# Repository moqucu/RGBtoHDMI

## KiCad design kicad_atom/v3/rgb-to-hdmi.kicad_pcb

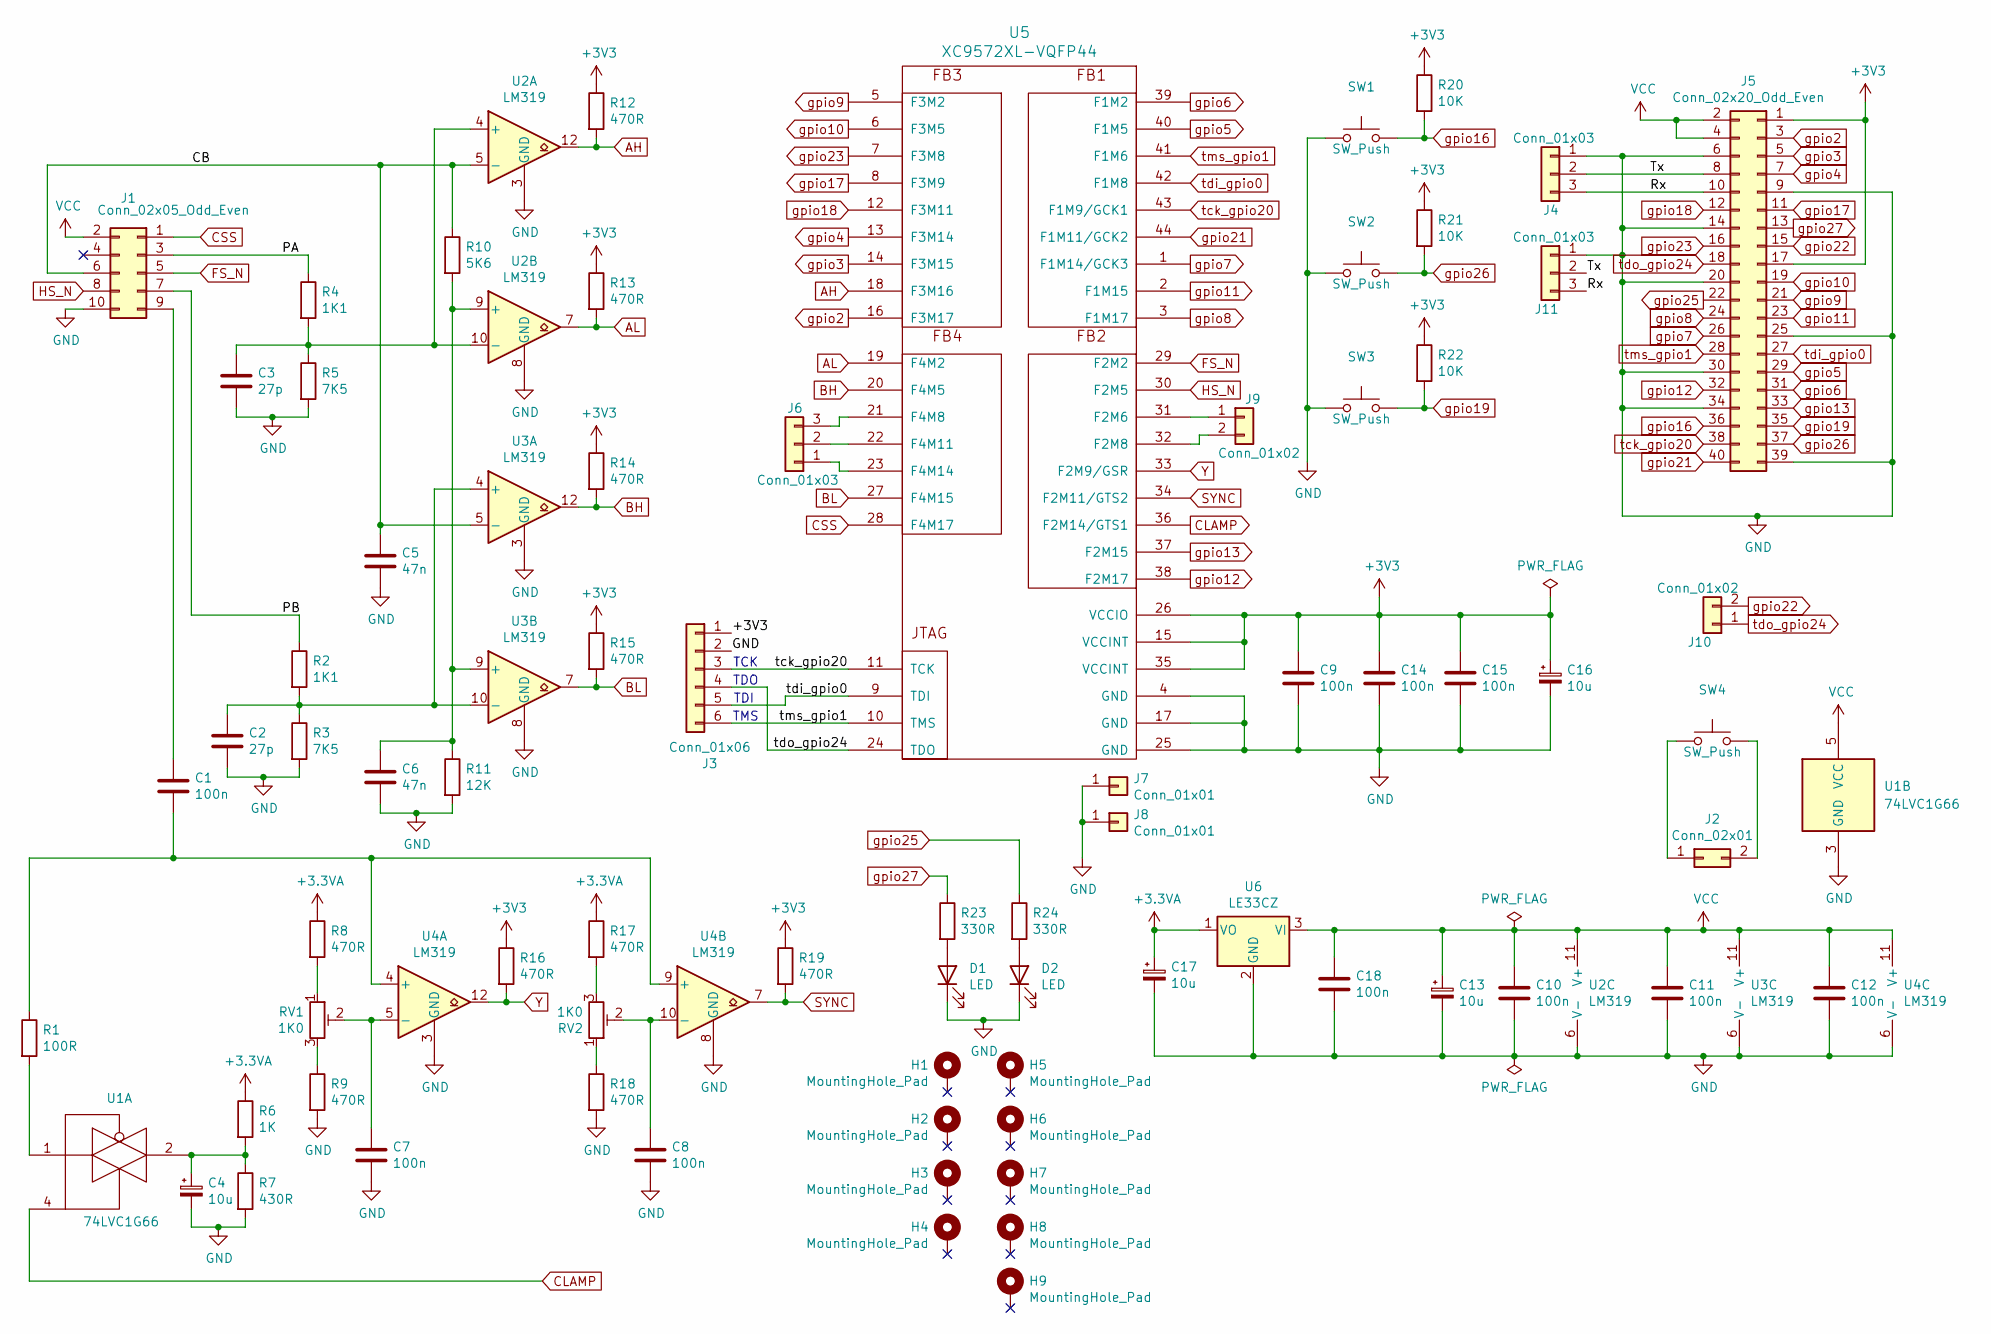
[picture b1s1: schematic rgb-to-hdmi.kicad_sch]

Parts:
C1, C7, C8, C18: 100n; C_Rect_L7.0mm_W2.5mm_P5.00mm
C2, C3: 27p; C_Rect_L7.0mm_W2.5mm_P5.00mm
C4, C13, C16, C17: 10u; CP_Radial_D5.0mm_P2.50mm
C5, C6: 47n; C_Rect_L7.0mm_W2.5mm_P5.00mm
C9, C14, C15: 100n; C_0805_2012Metric_Pad1.18x1.45mm_HandSolder
C10, C11, C12: 100n; C_Axial_L5.1mm_D3.1mm_P10.00mm_Horizontal
D1, D2: LED; LED_D3.0mm
H1, H2, H3, H4, H5, H6, H7, H8, H9: MountingHole_Pad; MountingHole_2.7mm_M2.5_Pad
J1: Conn_02x05_Odd_Even; IDC-Header_2x05_P2.54mm_Vertical
J2: Conn_02x01; PinSocket_1x02_P2.54mm_Vertical
J3: Conn_01x06; PinHeader_1x06_P2.54mm_Vertical
J4: Conn_01x03; PinHeader_1x03_P2.54mm_Horizontal
J5: Conn_02x20_Odd_Even; PinSocket_2x20_P2.54mm_Vertical
J6, J11: Conn_01x03; PinHeader_1x03_P2.54mm_Vertical
J7, J8: Conn_01x01; PinHeader_1x01_P2.54mm_Vertical
J9, J10: Conn_01x02; PinHeader_1x02_P2.54mm_Vertical
R1: 100R; R_Axial_DIN0207_L6.3mm_D2.5mm_P10.16mm_Horizontal
R2, R4: 1K1; R_Axial_DIN0207_L6.3mm_D2.5mm_P10.16mm_Horizontal
R3, R5: 7K5; R_Axial_DIN0207_L6.3mm_D2.5mm_P10.16mm_Horizontal
R6: 1K; R_Axial_DIN0207_L6.3mm_D2.5mm_P10.16mm_Horizontal
R7: 430R; R_Axial_DIN0207_L6.3mm_D2.5mm_P10.16mm_Horizontal
R8, R9, R12, R13, R14, R15, R16, R17, R18, R19: 470R; R_Axial_DIN0207_L6.3mm_D2.5mm_P10.16mm_Horizontal
R10: 5K6; R_Axial_DIN0207_L6.3mm_D2.5mm_P10.16mm_Horizontal
R11: 12K; R_Axial_DIN0207_L6.3mm_D2.5mm_P10.16mm_Horizontal
R20, R21, R22: 10K; R_Axial_DIN0207_L6.3mm_D2.5mm_P10.16mm_Horizontal
R23, R24: 330R; R_Axial_DIN0207_L6.3mm_D2.5mm_P10.16mm_Horizontal
RV1, RV2: 1K0; Potentiometer_Vishay_T73YP_Vertical
SW1, SW2, SW3: SW_Push; SW_TH_Tactile_Omron_B3F-100x
SW4: SW_Push; SW_Tactile_SKHH_Angled
U1: 74LVC1G66; SOT-23-5_HandSoldering
U2, U3, U4: LM319; DIP-14_W7.62mm_Socket_LongPads
U5: XC9572XL-VQFP44; LQFP-44_10x10mm_P0.8mm
U6: LE33CZ; TO-92_HandSolder

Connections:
+3.3VA: C17.1, R6.1, R8.1, R17.1, U6.1 (VO)
+3V3: C9.1, C14.1, C15.1, C16.1, J3.1, J5.1, J5.17, R12.1, R13.1, R14.1, R15.1, R16.1, R19.1, R20.1, R21.1, R22.1, U5.15 (VCCINT), U5.26 (VCCIO), U5.35 (VCCINT)
/CB: C5.1, J1.6, R10.1, U2.5 (-), U3.5 (-)
/PA: J1.3, R4.1
/PB: J1.7, R2.1
/Rx: J4.3, J5.10, J11.3
/Tx: J4.2, J5.8, J11.2
AH: R12.2, U2.12, U5.18 (F3M16)
AL: R13.2, U2.7, U5.19 (F4M2)
BH: R14.2, U3.12, U5.20 (F4M5)
BL: R15.2, U3.7, U5.27 (F4M15)
CLAMP: U1.4, U5.36 (F2M14/GTS1)
CSS: J1.1, U5.28 (F4M17)
FS_N: J1.5, U5.29 (F2M2)
GND: C2.2, C3.2, C4.2, C5.2, C6.2, C7.2, C8.2, C9.2, C10.2, C11.2, C12.2, C13.2, C14.2, C15.2, C16.2, C17.2, C18.2, D1.1 (K), D2.1 (K), J1.10, J3.2, J4.1, J5.6, J5.9, J5.14, J5.20, J5.25, J5.30, J5.34, J5.39, J7.1, J8.1, J11.1, R3.2, R5.2, R7.2, R9.2, R11.2, R18.2, SW1.1, SW2.1, SW3.1, U1.3 (GND), U2.3 (GND), U2.6 (V-), U2.8 (GND), U3.3 (GND), U3.6 (V-), U3.8 (GND), U4.3 (GND), U4.6 (V-), U4.8 (GND), U5.4 (GND), U5.17 (GND), U5.25 (GND), U6.2 (GND)
HS_N: J1.8, U5.30 (F2M5)
unnamed: C4.1, R6.2, R7.1, U1.2
unnamed: D1.2 (A), R23.2
unnamed: D2.2 (A), R24.2
unnamed: C1.1, J1.9
unnamed: J2.1, SW4.1
unnamed: J2.2, SW4.2
unnamed: J6.1, U5.23 (F4M14)
unnamed: J6.2, U5.22 (F4M11)
unnamed: J6.3, U5.21 (F4M8)
unnamed: J9.1, U5.31 (F2M6)
unnamed: J9.2, U5.32 (F2M8)
unnamed: R1.2, U1.1
unnamed: R8.2, RV1.1
unnamed: R9.1, RV1.3
unnamed: R17.2, RV2.3
unnamed: R18.1, RV2.1
unnamed: C3.1, R4.2, R5.1, U2.4 (+), U2.10 (-)
unnamed: C6.1, R10.2, R11.1, U2.9 (+), U3.9 (+)
unnamed: C2.1, R2.2, R3.1, U3.4 (+), U3.10 (-)
unnamed: C1.2, R1.1, U4.4 (+), U4.9 (+)
unnamed: C7.1, RV1.2, U4.5 (-)
unnamed: C8.1, RV2.2, U4.10 (-)
SYNC: R19.2, U4.7, U5.34 (F2M11/GTS2)
VCC: C10.1, C11.1, C12.1, C13.1, C18.1, J1.2, J5.2, J5.4, U1.5 (VCC), U2.11 (V+), U3.11 (V+), U4.11 (V+), U6.3 (VI)
Y: R16.2, U4.12, U5.33 (F2M9/GSR)
gpio2: J5.3, U5.16 (F3M17)
gpio3: J5.5, U5.14 (F3M15)
gpio4: J5.7, U5.13 (F3M14)
gpio5: J5.29, U5.40 (F1M5)
gpio6: J5.31, U5.39 (F1M2)
gpio7: J5.26, U5.1 (F1M14/GCK3)
gpio8: J5.24, U5.3 (F1M17)
gpio9: J5.21, U5.5 (F3M2)
gpio10: J5.19, U5.6 (F3M5)
gpio11: J5.23, U5.2 (F1M15)
gpio12: J5.32, U5.38 (F2M17)
gpio13: J5.33, U5.37 (F2M15)
gpio16: J5.36, R20.2, SW1.2
gpio17: J5.11, U5.8 (F3M9)
gpio18: J5.12, U5.12 (F3M11)
gpio19: J5.35, R22.2, SW3.2
gpio21: J5.40, U5.44 (F1M11/GCK2)
gpio22: J5.15, J10.2
gpio23: J5.16, U5.7 (F3M8)
gpio25: J5.22, R24.1
gpio26: J5.37, R21.2, SW2.2
gpio27: J5.13, R23.1
tck_gpio20: J3.3, J5.38, U5.11 (TCK), U5.43 (F1M9/GCK1)
tdi_gpio0: J3.5, J5.27, U5.9 (TDI), U5.42 (F1M8)
tdo_gpio24: J3.4, J5.18, J10.1, U5.24 (TDO)
tms_gpio1: J3.6, J5.28, U5.10 (TMS), U5.41 (F1M6)

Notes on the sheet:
TDO
TDI
TMS
TCK

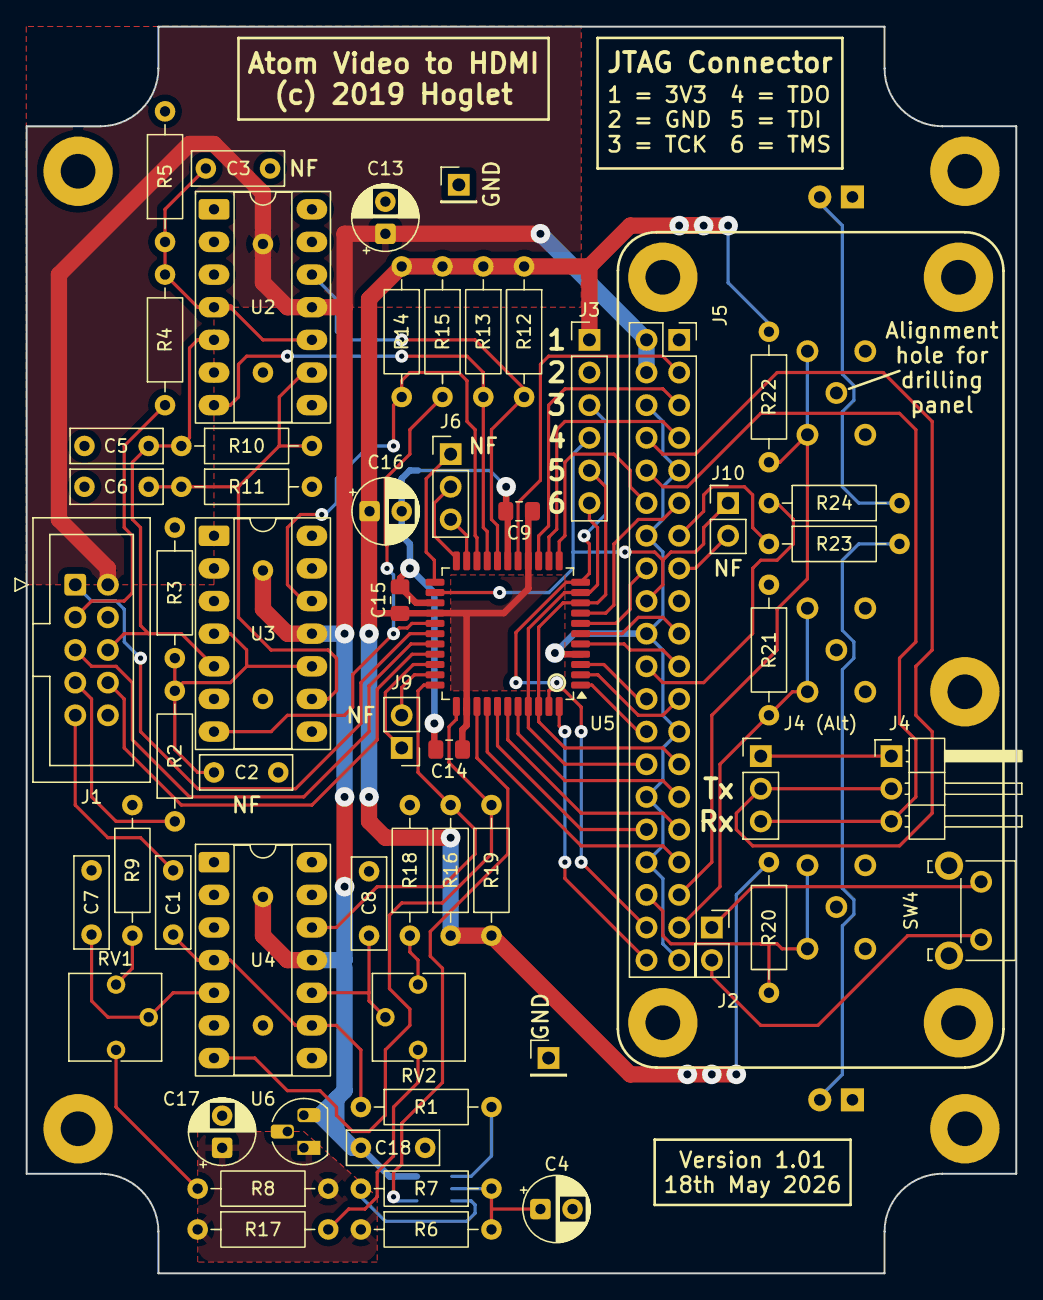
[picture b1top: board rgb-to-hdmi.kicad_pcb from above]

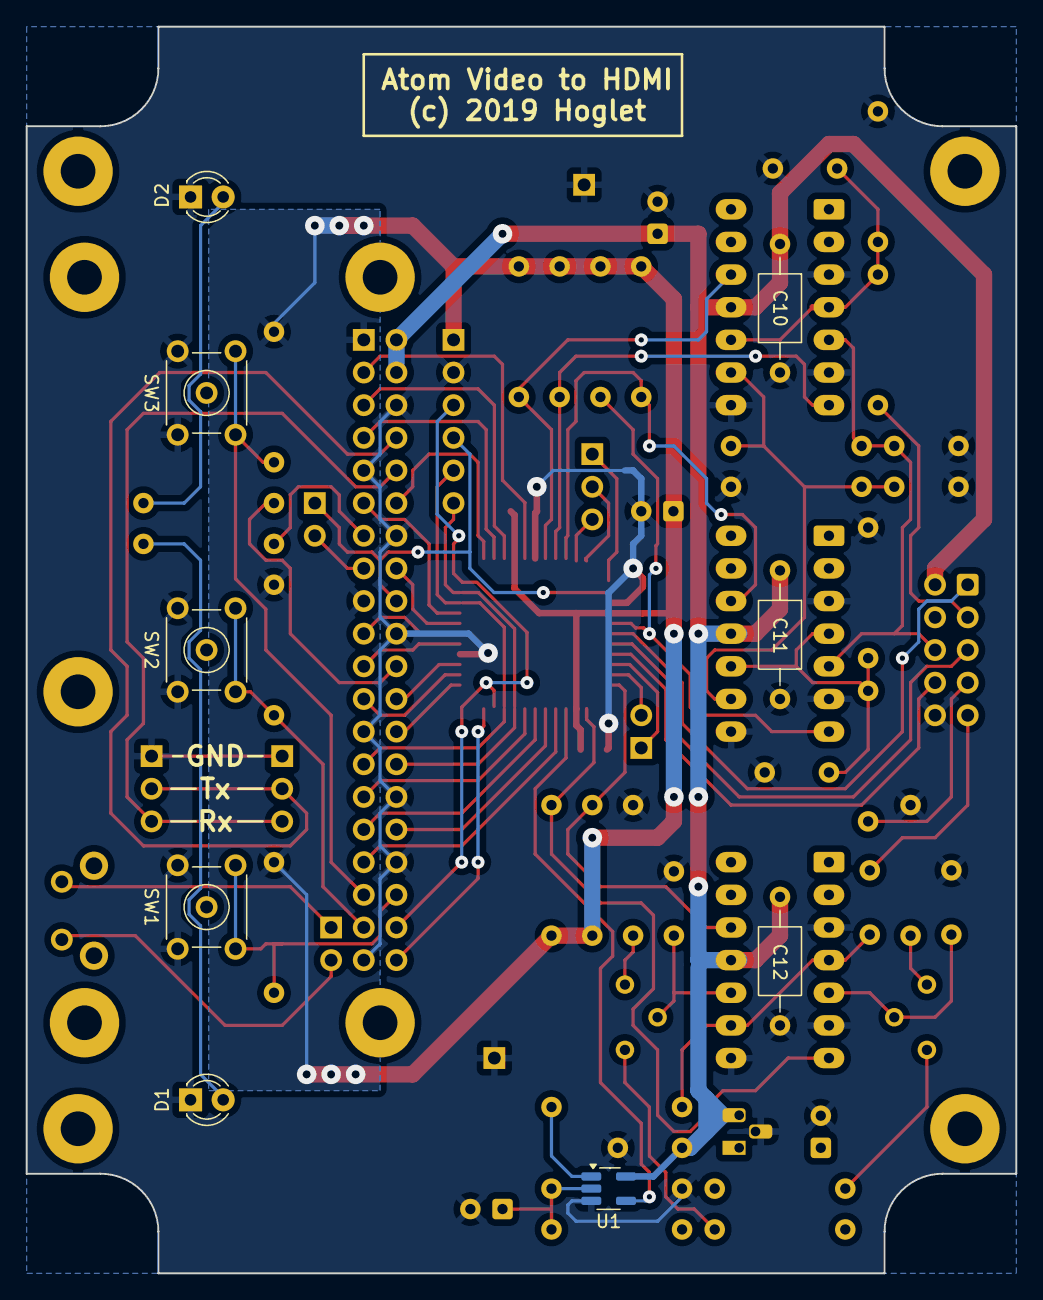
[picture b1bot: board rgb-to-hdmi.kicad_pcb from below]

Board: 2 copper layers, 77.0 x 97.0 mm, 76 parts (9 on the bottom side), 67 nets.

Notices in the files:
kicad_atom/v3/rgb-to-hdmi.kicad_pcb:
(c) 2019 Hoglet
